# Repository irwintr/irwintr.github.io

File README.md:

---
csl: apa.csl
bibliography: RPiCitations.bib
---

**ActiveHouse**
===============

Project website <https://irwintr.github.io>

Prepared by Trenton Irwin

March 28, 2017

  \pagebreak   \linespread{2} \selectfont

**Declaration of Sole Authorship**
----------------------------------

I, Trenton Irwin, will be completing all of the work related to this project
including the hardware, database, web service, and mobile application. Any uses
made within it of the works of any other author, in any form (ideas, equations,
figures, texts, tables, programs), are properly acknowledged at the point of
use. A list of the references used is included. It is mandatory that all sources
of information be acknowledged in the SRS. Plagiarism is unethical and a
candidate suspected of plagiarizing may be referred to the Complaints Committee.

  \pagebreak

**Proposal**
------------

### **Proposal Table of Contents**

1.  [Proposal](https://github.com/irwintr/irwintr.github.io/blob/master/README.md#proposal)

2.  [Executive
    Summary](https://github.com/irwintr/irwintr.github.io/blob/master/README.md#executive-summary)

3.  [Background](https://github.com/irwintr/irwintr.github.io/blob/master/README.md#background)

4.  [Methodology](https://github.com/irwintr/irwintr.github.io/blob/master/README.md#methodology)

5.  [Concluding
    Remarks](https://github.com/irwintr/irwintr.github.io/blob/master/README.md#concluding-remarks)

6.  [References](https://github.com/irwintr/irwintr.github.io/blob/master/README.md#references)

The ActiveHouse Project would be a complete home monitoring system consisting of
multiple Arduino based sensor hubs in each room of your home wirelessly
connecting to a Raspberry Pi based base station which sends the data to the
server where it can be read by the app. Each sensor hub would be capable of
reading temperature, humidity, luminosity, carbon monoxide and other gas levels,
water consumption, power consumption, and it would have the ability to toggle
the built-in light. The power and water consumption sensors are detachable as
they would not necessarily be used in each room, thus creating a more modular
design. The app would allow users to view the current settings in each room and
over the complete house, toggle the lighting, and set a lighting schedule.

\#\#\# **Executive Summary**
----------------------------

As a Computer Engineering student, I’ll be using all of the skills I have
learned in the last 2 years in this program to complete this project. This
proposal requests the approval to build the hardware portion that will connect
to a database as well as to a mobile device application. The sensor hub hardware
will include a custom PCB with sensors and XBee wireless adapters and an Arduino
inside a custom printed box. The Base station hardware will include an XBee
wireless adapter connected to a Raspberry Pi. The database will store the sensor
data from each room. The mobile device functionality will allow users to view
the current settings in each room and over the complete house, toggle the
lighting, and set a lighting schedule. I may end up collaborating with the
greater Active House team later in the semester but I will not be working with
any companies. The hardware will be completed in CENG 317 Hardware Production
Techniques independently and the application will be completed in CENG 319
Software Project. These will be integrated together in the subsequent term in
CENG 355 Computer Systems Project.

\#\#\# **Background**
---------------------

The problem solved by this project is that it provides a home monitoring
solution so that users homes can be controlled and monitored remotely through an
intuitive app. It will help people monitor their resource consumption as well
which may help drive down consumption.

There are several other home monitoring solutions on the market now[@4429263],
but they are usually integrated into either the thermostat or home security
system. This is one of the first projects I’ve seen where water and power
consumption are also monitored on a residential scale.

In the Computer Engineering Technology program I have learned about the
following topics from the respective relevant courses:

-   Electronic Devices and Circuits – Soldering experience

-   Database with Java – Setting up database

-   Electronic Circuits – Voltage Divider calculations

-   Technical Workplace Writing – Creating write-ups and technical drawings

-   Software Engineering – Creating project schedules

This knowledge and skill set will enable me to build the subsystems and
integrate them together as my capstone project.

\#\#\# **Methodology**
----------------------

This proposal is assigned in the first week of class and is due at the beginning
of class in the second week of the fall semester. My coursework will focus on
the first two of the 3 phases of this project:  
Phase 1 Hardware build.  
Phase 2 System integration.  
Phase 3 Demonstration to future employers.

~~~~~~~~~~~~~~~~~~~~~~~~~~~~~~~~~~~~~~~~~~~~~~~~~~~~~~~~~~~~~~~~~~~~~~~~~~~~~~~~
*Phase 1 Hardware build*
~~~~~~~~~~~~~~~~~~~~~~~~~~~~~~~~~~~~~~~~~~~~~~~~~~~~~~~~~~~~~~~~~~~~~~~~~~~~~~~~

The hardware build will be completed in the fall term. It will fit within the
CENG Project maximum dimensions of 12 13/16" x 6" x 2 7/8" (32.5cm x 15.25cm x
7.25cm) which represents the space below the tray in the parts kit. The highest
AC voltage that will be used is 16Vrms from a wall adaptor from which +/- 15V or
as high as 45 VDC can be obtained. Maximum power consumption will be 20 Watts.

~~~~~~~~~~~~~~~~~~~~~~~~~~~~~~~~~~~~~~~~~~~~~~~~~~~~~~~~~~~~~~~~~~~~~~~~~~~~~~~~
*Phase 2 System integration*
~~~~~~~~~~~~~~~~~~~~~~~~~~~~~~~~~~~~~~~~~~~~~~~~~~~~~~~~~~~~~~~~~~~~~~~~~~~~~~~~

The system integration will be completed in the winter term.

*Phase 3 Demonstration to future employers*

This project will showcase the knowledge and skills that we have learned to
potential employers.

The tables below provide rough effort and non-labour estimates respectively for
each phase. A Gantt chart will be added by week 3 to provide more project
schedule details and a more complete budget will be added by week 4. It is
important to start tasks as soon as possible to be able to meet deadlines.

| **Labour Estimates**                                                                      | **Hrs**      | **Notes**                                                                                                                      |
|-------------------------------------------------------------------------------------------|--------------|--------------------------------------------------------------------------------------------------------------------------------|
| **Phase 1**                                                                               |              |                                                                                                                                |
| Writing proposal.                                                                         | 9            | Tech identification quiz.                                                                                                      |
| Creating project schedule. Initial project team meeting.                                  | 9            | Proposal due.                                                                                                                  |
| Creating budget. Status Meeting.                                                          | 9            | Project Schedule due.                                                                                                          |
| Acquiring components and writing progress report.                                         | 9            | Budget due.                                                                                                                    |
| Mechanical assembly and writing progress report. Status Meeting.                          | 9            | Progress Report due (components acquired milestone).                                                                           |
| PCB fabrication.                                                                          | 9            | Progress Report due (Mechanical Assembly milestone).                                                                           |
| Interface wiring, Placard design, Status Meeting.                                         | 9            | PCB Due (power up milestone).                                                                                                  |
| Preparing for demonstration.                                                              | 9            | Placard due.                                                                                                                   |
| Writing progress report and demonstrating project.                                        | 9            | Progress Report due (Demonstrations at Open House Saturday, November 7, 2015 from 10 a.m. - 2 p.m.).                           |
| Editing build video.                                                                      | 9            | Peer grading of demonstrations due.                                                                                            |
| Incorporation of feedback from demonstration and writing progress report. Status Meeting. | 9            | 30 second build video due.                                                                                                     |
| Practice presentations                                                                    | 9            | Progress Report due.                                                                                                           |
| 1st round of Presentations, Collaborators present.                                        | 9            | Presentation PowerPoint file due.                                                                                              |
| 2nd round of Presentations                                                                | 9            | Build instructions up due.                                                                                                     |
| Project videos, Status Meeting.                                                           | 9            | 30 second script due.                                                                                                          |
| **Phase 1 Total**                                                                         | **135**      |                                                                                                                                |
| **Phase 2**                                                                               |              |                                                                                                                                |
| Meet with collaborators                                                                   | 9            | Status Meeting                                                                                                                 |
| Initial integration.                                                                      | 9            | Progress Report                                                                                                                |
| Meet with collaborators                                                                   | 9            | Status Meeting                                                                                                                 |
| Testing.                                                                                  | 9            | Progress Report                                                                                                                |
| Meet with collaborators                                                                   | 9            | Status Meeting                                                                                                                 |
| Meet with collaborators                                                                   | 9            | Status Meeting                                                                                                                 |
| Incorporation of feedback.                                                                | 9            | Progress Report                                                                                                                |
| Meet with collaborators                                                                   | 9            | Status Meeting                                                                                                                 |
| Testing.                                                                                  | 9            | Progress Report                                                                                                                |
| Meet with collaborators                                                                   | 9            | Status Meeting                                                                                                                 |
| Prepare for demonstration.                                                                | 9            | Progress Report                                                                                                                |
| Complete presentation.                                                                    | 9            | Demonstration at Open House Saturday, April 9, 2016 10 a.m. to 2 p.m.                                                          |
| Complete final report. 1st round of Presentations.                                        | 9            | Presentation PowerPoint file due.                                                                                              |
| Write video script. 2nd round of Presentations, delivery of project.                      | 9            | Final written report including final budget and record of expenditures, covering both this semester and the previous semester. |
| Project videos.                                                                           | 9            | Video script due                                                                                                               |
| **Phase 2 Total**                                                                         | **135**      |                                                                                                                                |
| **Phase 3**                                                                               |              |                                                                                                                                |
| Interviews                                                                                | TBD          |                                                                                                                                |
| **Phase 3 Total**                                                                         | **TBD**      |                                                                                                                                |
| **Material Estimates**                                                                    | **Cost**     | **Supplier**                                                                                                                   |
| **Phase 1**                                                                               |              |                                                                                                                                |
| Cannakit Raspberry Pi v3                                                                  | \$99.99      | Amazon.ca                                                                                                                      |
| Arduino Uno SMD Rev3                                                                      | \$31.08      | Digi-key                                                                                                                       |
| Xbee S1 Trace Antenna (x2)                                                                | \$53.68      | Digi-key                                                                                                                       |
| Xbee Shield for Arduino                                                                   | \$22.77      | Digi-key                                                                                                                       |
| 3.5mm audio jack                                                                          | \$2.09       | Canada Robotix                                                                                                                 |
| Non-Invasive Current Sensor                                                               | \$13.19      | Canada Robotix                                                                                                                 |
| Adafruit Gas Sensor                                                                       | \$21.12      | Digi-key                                                                                                                       |
| Adafruit Light Sensor                                                                     | \$8.40       | Digi-key                                                                                                                       |
| Water Flow Sensor                                                                         | \$11.89      | Canada Robotix                                                                                                                 |
| 3 Pin Molex header                                                                        | \$0.39       | Canada Robotix                                                                                                                 |
| 12mm Buzzer                                                                               | \$1.99       | Canada Robotix                                                                                                                 |
| Adafruit Temperature and Humidity Sensor                                                  | \$19.70      | Digi-key                                                                                                                       |
| *Shipping*                                                                                | *\$6.95*     |                                                                                                                                |
| *Tax*                                                                                     | *\$37.22*    |                                                                                                                                |
| **Phase 1 Total**                                                                         | **\$330.46** |                                                                                                                                |
| **Phase 2**                                                                               |              |                                                                                                                                |
| Materials to improve functionality, fit, and finish of project.                           | N/A          |                                                                                                                                |
| **Phase 2 Total**                                                                         | **TBD**      |                                                                                                                                |
| **Phase 3**                                                                               |              |                                                                                                                                |
| **Phase 3 Total**                                                                         | **TBD**      |                                                                                                                                |

\#\#\# **Concluding remarks**
-----------------------------

This proposal presents a plan for providing an IoT solution for a home
monitoring system. This is an opportunity to integrate the knowledge and skills
developed in the Computer Engineering program to create a collaborative IoT
capstone project demonstrating my ability to learn how to support projects. I
request approval of this project.

  \pagebreak

**Abstract**
------------

This report contains information outlining the ActiveHouse home monitoring
system project. The project aims to create a complete home enviromental
monitoring system to measure temperature, humidity, light levels, water
consumption, power consumption, smoke and gas detection, and the ability to
toggle lights. There is an Android mobile application for displaying the data
and making changes. The hardware consists of a Raspberry Pi, an Arduino, xBee
wireless adapters, and a mirriad of sensors. The web service and database to
store all the data is hosted on Munro.humber.ca. The total cost for the
prototype is about \$330. The project will take me about 8 months to complete
but can be redone in much less time.  

  \pagebreak

**Table of Contents**
---------------------

1.  [Declaration of Sole
    Authorship](https://github.com/irwintr/irwintr.github.io/blob/master/README.md#declaration-of-sole-authorship)

2.  [Proposal](https://github.com/irwintr/irwintr.github.io/blob/master/README.md#proposal)

3.  [Abstract](https://github.com/irwintr/irwintr.github.io/blob/master/README.md#abstract)

4.  [Table of
    Contents](https://github.com/irwintr/irwintr.github.io/blob/master/README.md#table-of-contents)

5.  [List of Illustrations or
    Diagrams](https://github.com/irwintr/irwintr.github.io/blob/master/README.md#list-of-illustrations-or-diagrams)

6.  [Introduction](https://github.com/irwintr/irwintr.github.io/blob/master/README.md#introduction)

7.  [Project
    Description](https://github.com/irwintr/irwintr.github.io/blob/master/README.md#project-description)

8.  [Conclusion](https://github.com/irwintr/irwintr.github.io/blob/master/README.md#conclusion)

9.  [Appendicies](https://github.com/irwintr/irwintr.github.io/blob/master/README.md#appendicies)

10. [Bibliography](https://github.com/irwintr/irwintr.github.io/blob/master/README.md#bibliography)

  \pagebreak

**List of Illustrations or Diagrams**
-------------------------------------

1.  Project Workflow diagram

2.  Budget / Parts list

3.  XBee breakout board

4.  XBee to Pi wiring diagram

5.  Sensor Hub

6.  ​Sensor Hub

7.  ​Sensor Hub

8.  ​Sensor Hub

9.  Raspberry Pi base station

10. Sensor Hub

11. ​Sensor Hub

12. Sample output from sensor hub

13. Sensor hub with sensors attached

\pagebreak

**Introduction**
----------------

The ActiveHouse Project is a complete home monitoring system consisting of
multiple Arduino based sensor hubs in each room of your home wirelessly
connecting to a Raspberry Pi based base station which sends the data to the
server where it can be read by the app. Each sensor hub is be capable of reading
temperature, humidity, luminosity, carbon monoxide and other gas levels, water
consumption, power consumption, and it would have the ability to toggle the
built-in light. The power and water consumption sensors are detachable as they
would not necessarily be used in each room, thus creating a more modular design.
The app allows users to view the current settings in each room and over the
complete house, toggle the lighting, and set a lighting schedule.

  \pagebreak

**Project Description**
-----------------------

The ActiveHouse project consists of two main pieces of hardware:

Raspberry Pi based base station with an Xbee wireless antenna connected to it.

Arduino based sensor hub which includes the following:

–Xbee Wireless Antenna

–Light Sensor

–Gas Sensor

–Current Sensor

–Water Flow Sensor

–Temperature Sensor

–Humidity Sensor

–Remote Controllable Light

–Buzzer

You can have as may sensor hubs as you want hooked up to one base station, they
jut need to be within the 300 foot range for the XBees.

There are 5 main software components at work in the Active House system; the
Arduino code running on the Sensor Hubs, the C++ code running on the Raspberry
Pi base station, the PHP Web Service Running on Munro, the MySQL database on
Munro, and the mobile Android app.

### **Sensor Hub Code​**

**Arduino Specifications**

The Arduino program communicates with the Base station over the XBee serial
communication to send sensor data and toggle the light status.

**Code​ Breakdown**

The program is written to initialize all of the sensors. After that, it waits
and listens on the XBee serial port for communication from the base station.
When it receives a message from the base station that includes that sensor hub’s
unique ID, it replies with all of the sensor data.

### **Base Station Code​**

**Raspberry Pi​ Specifications**

The Raspberry Pi based Base Station is used to communicate with the Sensor Hubs
over the XBee serial communication to gather all of the sensor data and send it
to the web service running on Munro.

\*\* Code​ Breakdown\*\*

The code that is running on the Raspberry Pi is written in C++ using the
ArduPi.cpp library which makes it easier to communicate using the Xbee. The
service has a list of the registered sensor hubs, and goes in order,
broadcasting each RoomID over the Xbee. When the corresponding sensor hub
receives this message, it will reply with all of its sensor data. The Base
Station code then parses that response and sends it back to the web service that
is running on Munro.

### Database Specifications

**Database Type**

For the ActiveHouse project I am using a MySQL database hosted on Munro. It can
be administered through phpMyAdmin.

**Database Tables**

There are four tables that are used in the Firebase.

1.  USERS

2.  HOUSE

3.  ROOM

4.  ROOM\_DATA

**USERS** is the table in which all users who sign up for the ActiveHouse
application are stored. They are given a key as a unique identifier.

**HOUSE** is the table in which the names of houses and their data are stored.
Each house is unique via an HOUSEID identification key within the table.

**ROOM** is the table in which the rooms in each house are stored. It contains
the HOUSEID that it corresponds with, a unique ROOMID and the room name.

**ROOM\_DATA** is the table where the sensor readings for each room are stored.
It is identified by the unique ROOMID.

**Work Breakdown**

There is no further work that needs to be done to the database.

### **Mobile Application Specifications**

**Graphical User Interface Specifications**

**MainActivity:** The login screen of the application is the first presented
upon launching the application. The user may enter already existing credentials
into EditText fields and login, or may choose to go to the sign up activity,
both navigations via Buttons. There is a checkbox to save the entered username
to local storage to be auto populated in future sessions.

**RegisterActivity:** The sign up screen of the application can be accessed from
the login screen. It has EditText fields for gathering new user information
including their HOUSEID. Without a HOUSEID, they cannot create a new account.
Incorrect EditText entries will be communicated via Toast message asking for
re-entry.

**HomeActivity:** This is the main screen of the app where the user can view the
current settings of the user’s house. There is a hamburger menu with links to
the other pages including one for each room in the home. Users can logout from
the menu bar.

**RoomActivity:** This page has the sensor data from an individual room
displayed. The user can interact with the page by toggling the light or light
schedule or setting the time on or off for the light. There is a hamburger menu
with links to the other pages including one for each room in the home. Users can
logout from the menu bar.

**RoomViewActivity:** The room view activity is a listview with all of the rooms
in it. Users can select the room they wish to view and be taken to the
RoomActivity page for that room.

**Application Work Breakdown**

There are a few small bugs that I need to patch, but the app is working and
pretty much complete.

### **Web Specifications**

**Web Service Specifications**

The web service is written in php and hosted on Munro. It can be accessed at
munro.humber.ca/\~n01046059/ActiveHouse.

**Web Work Breakdown**

The side of the web service that interacts with the mobile app is complete and
does not require any changes. I do need to write the side of the web service
that connects to the Raspberry Pi to send and receive sensor data. Additionally
I need to write a program to run on the Raspberry Pi to send the data to the
server.

\pagebreak

### **Build Instructions**

My Active House project is a complete home monitoring system. The idea is that
you would have one Sensor Hub in each room of your home to collect data You
would have one Raspberry Pi based base station which all of the sensor hubs send
their data wirelessly to. The base station then sends the received sensor data
to the database for use in my app.

#### Parts:

Here is a list of all the parts and aproximate costs for one Raspberry Pi base
station and one Sensor Hub:

This list does not include parts from the Humber electronics parts kit. The
parts you will need from the kit are:

-   220ohm Resistor

-   33ohm Resistor

-   2x 10Kohm Resistors

-   LED

-   50uf Capacitor

-   Single Core Wire

You will also need to print out the Acrylic case which can be found
[here](https://github.com/irwintr/irwintr.github.io/tree/master/Case) and the 2
PCBs which can be found
[here](https://github.com/irwintr/irwintr.github.io/tree/master/ArdunioShield)
and
[here](https://github.com/irwintr/irwintr.github.io/tree/master/XBeeBreakout).

#### Time Commitment

While it took me probably upwards of 30 hours to design the project and the
circuit boards, put it all together, and code it, I'd expect it to only take
around 5 hours to build the project again.

#### PCB/Soldering

The first board you will need to solder is the XBee Breakout board. You only
need to solder the 3.3v, GND, RX and TX pins as seen in this diagram:

Then you will need to solder the Arduino Shield which includes all of the
sensors and connections. You can view the board and schematic files for this
board
[here](https://github.com/irwintr/irwintr.github.io/tree/master/ArdunioShield)
which will explain where all of the components and connections go. Beware, some
of the solder pads on the Arduin Shield are very small and you will need a very
steady hand to solder them. Below are a collection of images which will help you
understand where everything goes and how it is connected:

#### Mechanical Assembly

First, you will need to unbox your Raspberry Pi and set it up. You can view my
unboxing video [here](#Section_2). After that, connect the wires from the Xbee
breakout board to the appropriate GPIO pins.

Next you will need to build your acrylic case for your Arduino. Glue the all but
the back side together and glue the ports for the current and liquid sensors
onto the rear panel of the case.

#### Code

You can view the Arduino Code
[here](https://github.com/irwintr/irwintr.github.io/tree/master/ArduinoCode) to
read all of the sensor data and output it to Serial. You will also need to
include the Libraries folder. Due to a limitation with the Arduino Uno and the
Arduino XBee Shield, you cannot upload code to the Arduino while the XBee shield
is plugged in, so it needs to be removed from the arduino board when uploading.
Alternativly, you could flash the Arduino Uno's bootloader with the Duemilanove
which supports uploading code over XBee and send the code to the Arduino
wirelessly from the Raspberry Pi. You can read about how to flash the bootloader
[here](https://learn.sparkfun.com/tutorials/installing-an-arduino-bootloader)

#### Power Up

The output from the Arduino is below. You can also view my power up in my Build
Video.

#### Testing

In all of the testing I have done so far, everything works as expected. I've
checked the read values from the temperature, humidity, light, and gas sensors
and they all seem to be accurate. I have noth been able to find a 1/2" hose to
connect to my liquid flow sensor so I've been unable to calibrate it, but
tripping it by blowing air trough it works as expected. I've tested the current
sensor with a few different appliances and its's read values seem to be close to
the expected range, howeer I still need to completely calibrate it with an
clampmeter. The buzzer and LED can both be toggled from within the code.

\pagebreak

**Conclusions**
---------------

 The ActiveHouse project is nearly complete and will be within the next week. It
was definately a learning experience, but I fell like it was a sucessful
project. There are a few things I might do differently next time including
adding a Sync button to both the base station and the sensor boxes to pair them
automatically, however my current method of pairing works just fine. All of the
components of the project are working flawlessly together as expected, there is
just a bit of coding left to be done. The ActiveHouse project has great
potential as a home monitoring system as it has many features included such as
water and power consumption monitoring that aren't included in commercial
solutions that are currently on the market. Unfortunately, the fact that it's
build using mainly consumer hardware such as the Raspberry Pi and the Arduino
makes it not financially viable to birng to market without compltetely
rebuilding it all using cheaper microcontrollers. It was still a very good
learning experience and the skills that I have learned on this project will keep
me tinkering with electronics for years to come.  

\pagebreak

**Appendicies**
---------------

  \pagebreak

**Bibliography**
----------------

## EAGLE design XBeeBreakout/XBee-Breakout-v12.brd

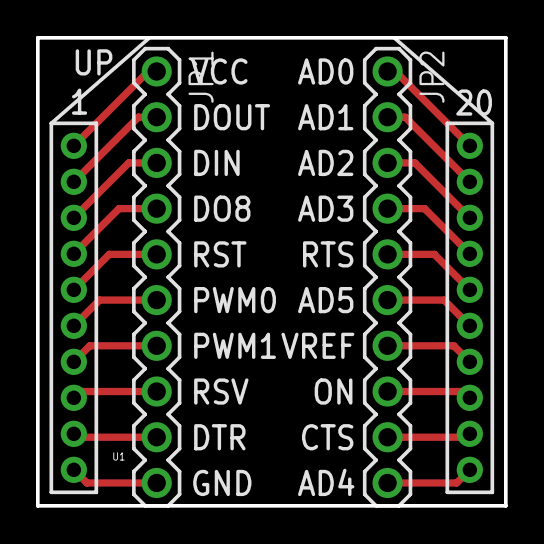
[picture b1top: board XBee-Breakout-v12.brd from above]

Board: 2 copper layers, 26.0 x 26.0 mm, 4 parts (1 on the bottom side), 20 nets.

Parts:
JP1, JP2: 1X10
U1: XBEE; XBEE-1
U$2: LOGO-SFENEW; SFE-NEW-WEBLOGO

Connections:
unnamed: JP1.5, U1.5
unnamed: JP1.1, U1.1
unnamed: JP1.2, U1.2
unnamed: JP1.3, U1.3
unnamed: JP1.4, U1.4
unnamed: JP1.6, U1.6
unnamed: JP1.7, U1.7
unnamed: JP1.8, U1.8
unnamed: JP1.9, U1.9
unnamed: JP1.10, U1.10
unnamed: JP2.10, U1.11
unnamed: JP2.9, U1.12
unnamed: JP2.8, U1.13
unnamed: JP2.7, U1.14
unnamed: JP2.6, U1.15
unnamed: JP2.5, U1.16
unnamed: JP2.4, U1.17
unnamed: JP2.3, U1.18
unnamed: JP2.2, U1.19
unnamed: JP2.1, U1.20

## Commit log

2016-09-06 :space_invader: Added .gitattributes & .gitignore files
2016-09-06 Revert ":space_invader: Added .gitattributes & .gitignore files"
    This reverts commit 1e785c4f12e45f8c099dceb4b40f80ff7dee7e10.
2016-09-20 Raspberry Pi Lights
2016-10-04 Web template
2016-10-11 Update Oct 11
2016-10-11 Updated quick links
2016-10-18 Fixed video
2016-11-01 Uploading build video
2016-11-02 Edited page
2016-11-08 Week 10 Progress Report
2016-11-08 Fixed link
2016-11-15 Week 11
2016-11-22 Week 12 Update
2016-11-22 Update week 12
2016-11-23 Added Schematic and gerbers for xbee breakout
2016-11-30 Added presentation
2016-11-30 Updated Project schedule
2016-12-05 added updated budget
2016-12-07 Build Log
2016-12-07 updated link
2016-12-13 30 second script
2017-01-18 readme update
2017-01-18 added readme.pdf
2017-01-18 page update
2017-01-24 FIxed readme.md
2017-01-24 update to citation
2017-01-26 Update to md file
2017-02-27 Added build instructions to readme.md
2017-02-27 update readme.md formatting
2017-03-29 updated technical report
2017-04-18 Added final presentation
2017-04-18 Updated presentation
